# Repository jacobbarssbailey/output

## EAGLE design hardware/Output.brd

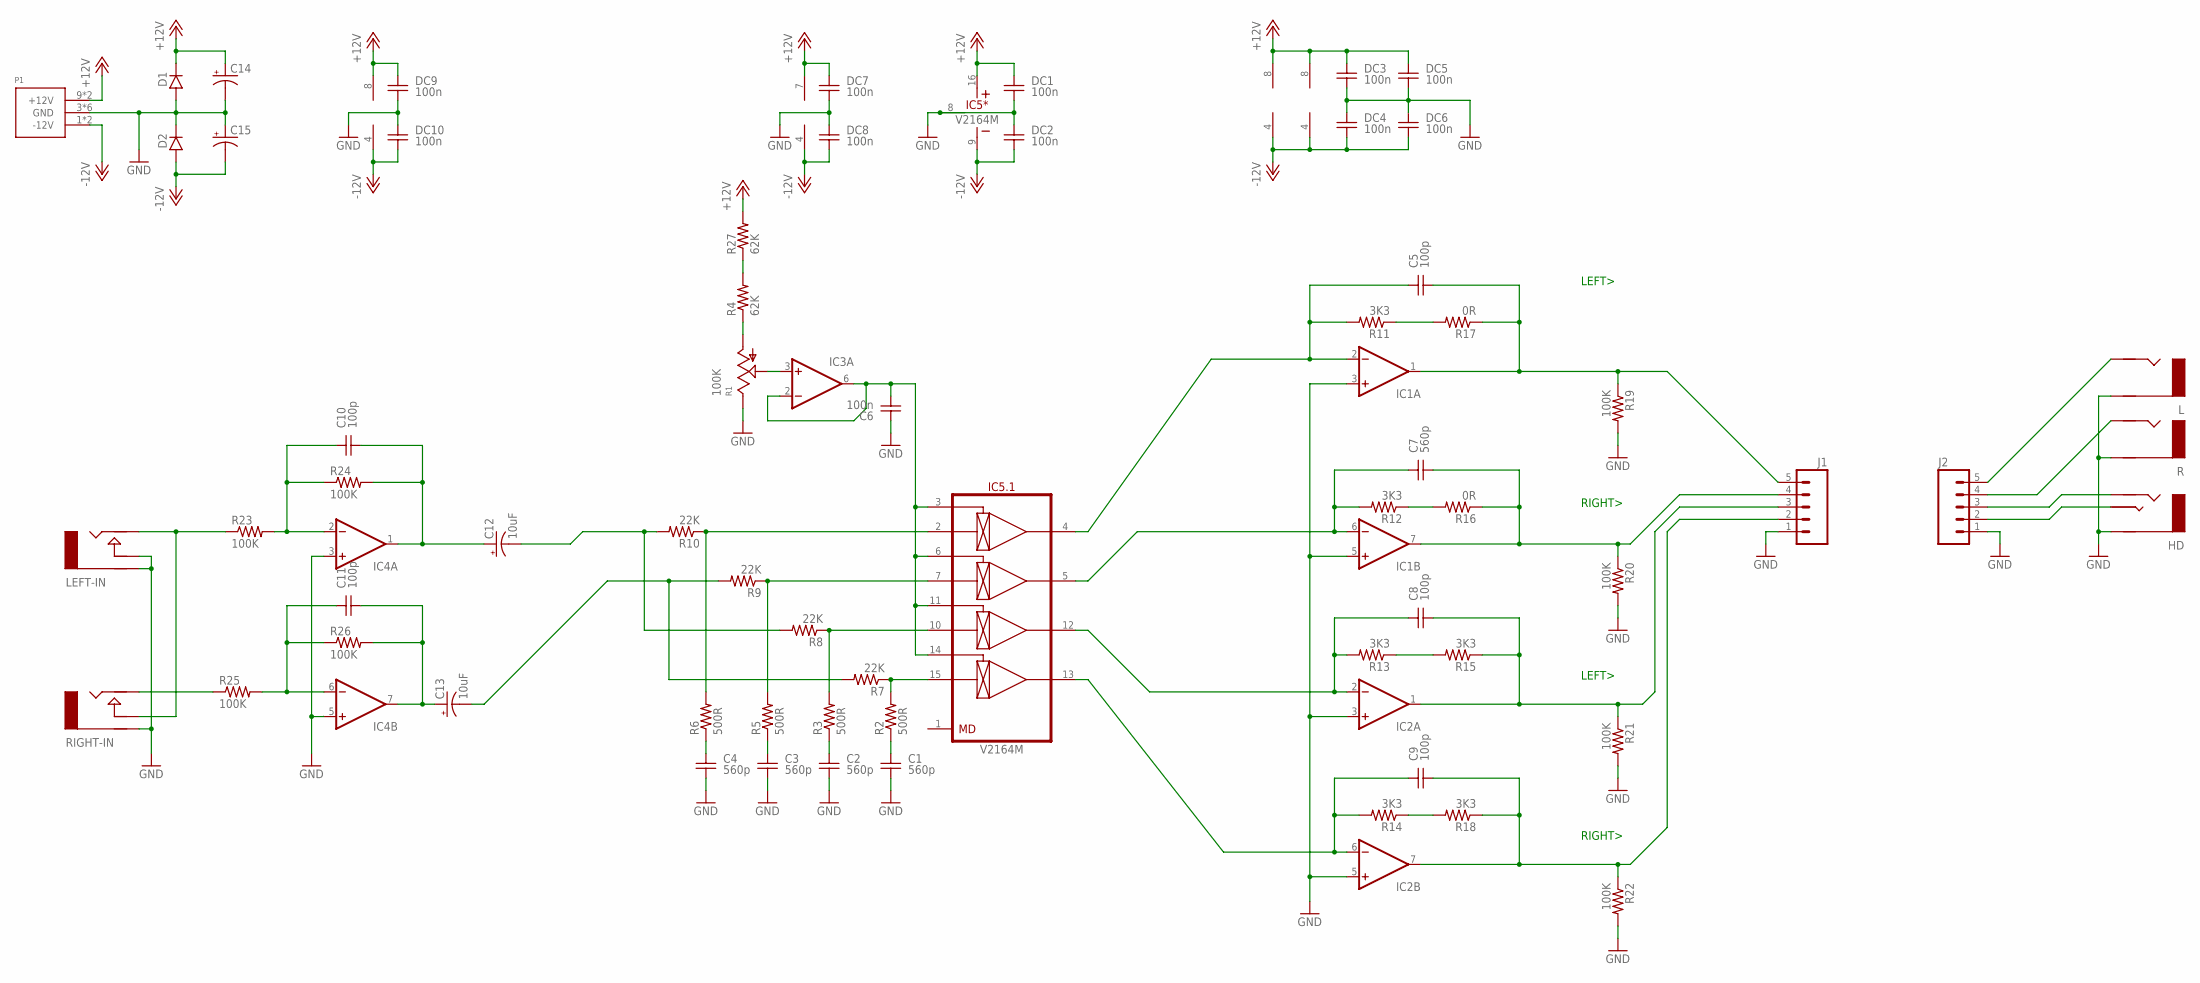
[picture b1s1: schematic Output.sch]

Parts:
C1, C2, C3, C4, C7: 560p; C-0805
C5, C8, C9, C10, C11: 100p; C-0805
C6: 100n; C-0805
C12, C13: 10uF; PANASONIC_C
C14, C15: CAP_POLPTH2; CPOL-RADIAL-10UF-25V
D1, D2: DIODESMA; SMA
DC1, DC2, DC3, DC4, DC5, DC6, DC7, DC8, DC9, DC10: 100n; C-0805
HD: AUDIO-JACK_STEREO; NJ3FD
IC1, IC2, IC4: OPAMP-DUAL; SO08
IC3: OPAMP-SINGLE; SO08
IC5: V2164M; SO-16
J1: CONN2; 1X05_LOCK
J2: CONN; 1X05_LOCK
L: AUDIO-JACK-MONO; NJ2FD
LEFT-IN: AUDIO-JACKINLINE; ERTHENVAR-JACK-INLINE
P1: POWER_SIMPLE10_SHROUDED; POWER_10_SHROUDED
R: AUDIO-JACK-MONO; NJ2FD
R1: 100K; POT-ALPHA-9MM
R2, R3, R5, R6: 500R; R-0805-MILL
R4, R27: 62K; R-0805-MILL
R7, R8, R9, R10: 22K; R-0805-MILL
R11, R12, R13, R14, R15, R18: 3K3; R-0805-MILL
R16, R17: 0R; R-0805-MILL
R19, R20, R21, R22, R23, R24, R25, R26: 100K; R-0805-MILL
RIGHT-IN: AUDIO-JACKINLINE; ERTHENVAR-JACK-INLINE

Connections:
+12V: C14.1 (+), D1.K (C), DC1.1, DC3.1, DC5.1, DC7.1, DC9.1, IC1.8 (V+), IC2.8 (V+), IC3.7 (V+), IC4.8 (V+), IC5.16 (V+), P1.9 (+12V), P1.10 (+12V), R27.P$2 (2)
-12V: C15.2 (-), D2.A, DC2.2, DC4.2, DC6.2, DC8.2, DC10.2, IC1.4 (V-), IC2.4 (V-), IC3.4 (V-), IC4.4 (V-), IC5.9 (V-), P1.1 (-12V), P1.2 (-12V)
GND: C1.2, C2.2, C3.2, C4.2, C6.1, C14.2 (-), C15.1 (+), D1.A, D2.K (C), DC1.2, DC2.1, DC3.2, DC4.1, DC5.2, DC6.1, DC7.2, DC8.1, DC9.2, DC10.1, HD.R (RING), IC1.3 (+IN), IC1.5 (+IN), IC2.3 (+IN), IC2.5 (+IN), IC4.3 (+IN), IC4.5 (+IN), IC5.8 (GND), J1.1, J2.1, L.S (RING), LEFT-IN.G (RING), LEFT-IN.N (NORM), P1.3 (GND), P1.4 (GND), P1.5 (GND), P1.6 (GND), P1.7 (GND), P1.8 (GND), R.S (RING), R1.B (E), R19.P$2 (2), R20.P$2 (2), R21.P$2 (2), R22.P$2 (2), RIGHT-IN.G (RING)
LEFT-IN: LEFT-IN.T (TIP), R23.P$1 (1), RIGHT-IN.N (NORM)
LEFT-IN-BUFF: C12.-, R8.P$2 (2), R10.P$2 (2)
unnamed: R1.A, R4.P$1 (1)
unnamed: IC5.2 (IN1), R6.P$2 (2), R10.P$1 (1)
unnamed: C6.2, IC3.2 (-IN), IC3.6 (OUT), IC5.3 (CV1), IC5.6 (CV2), IC5.11 (CV3), IC5.14 (CV4)
unnamed: IC5.7 (IN2), R5.P$2 (2), R9.P$1 (1)
unnamed: IC5.10 (IN3), R3.P$2 (2), R8.P$1 (1)
unnamed: IC5.15 (IN4), R2.P$2 (2), R7.P$1 (1)
unnamed: C1.1, R2.P$1 (1)
unnamed: J2.5, L.T (TIP)
unnamed: C2.1, R3.P$1 (1)
unnamed: C3.1, R5.P$1 (1)
unnamed: C4.1, R6.P$1 (1)
unnamed: R14.P$1 (1), R18.P$2 (2)
unnamed: C9.2, IC2.7 (OUT), J1.2, R18.P$1 (1), R22.P$1 (1)
unnamed: J2.4, R.T (TIP)
unnamed: C5.1, IC1.2 (-IN), IC5.4 (OUT1), R11.P$2 (2)
unnamed: C7.1, IC1.6 (-IN), IC5.5 (OUT2), R12.P$2 (2)
unnamed: C8.1, IC2.2 (-IN), IC5.12 (OUT3), R13.P$2 (2)
unnamed: C9.1, IC2.6 (-IN), IC5.13 (OUT4), R14.P$2 (2)
unnamed: C5.2, IC1.1 (OUT), J1.5, R17.P$1 (1), R19.P$1 (1)
unnamed: IC3.3 (+IN), R1.W (S)
unnamed: R13.P$1 (1), R15.P$2 (2)
unnamed: C7.2, IC1.7 (OUT), J1.4, R16.P$1 (1), R20.P$1 (1)
unnamed: R12.P$1 (1), R16.P$2 (2)
unnamed: C8.2, IC2.1 (OUT), J1.3, R15.P$1 (1), R21.P$1 (1)
unnamed: R11.P$1 (1), R17.P$2 (2)
unnamed: HD.T (TIP), J2.3
unnamed: HD.S (SLEEVE), J2.2
unnamed: C10.1, IC4.2 (-IN), R23.P$2 (2), R24.P$1 (1)
unnamed: C11.1, IC4.6 (-IN), R25.P$2 (2), R26.P$1 (1)
unnamed: C10.2, C12.+, IC4.1 (OUT), R24.P$2 (2)
unnamed: C11.2, C13.+, IC4.7 (OUT), R26.P$2 (2)
unnamed: R4.P$2 (2), R27.P$1 (1)
RIGHT-IN: R25.P$1 (1), RIGHT-IN.T (TIP)
RIGHT-IN-BUFF: C13.-, R7.P$2 (2), R9.P$2 (2)

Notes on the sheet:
LEFT>
RIGHT>

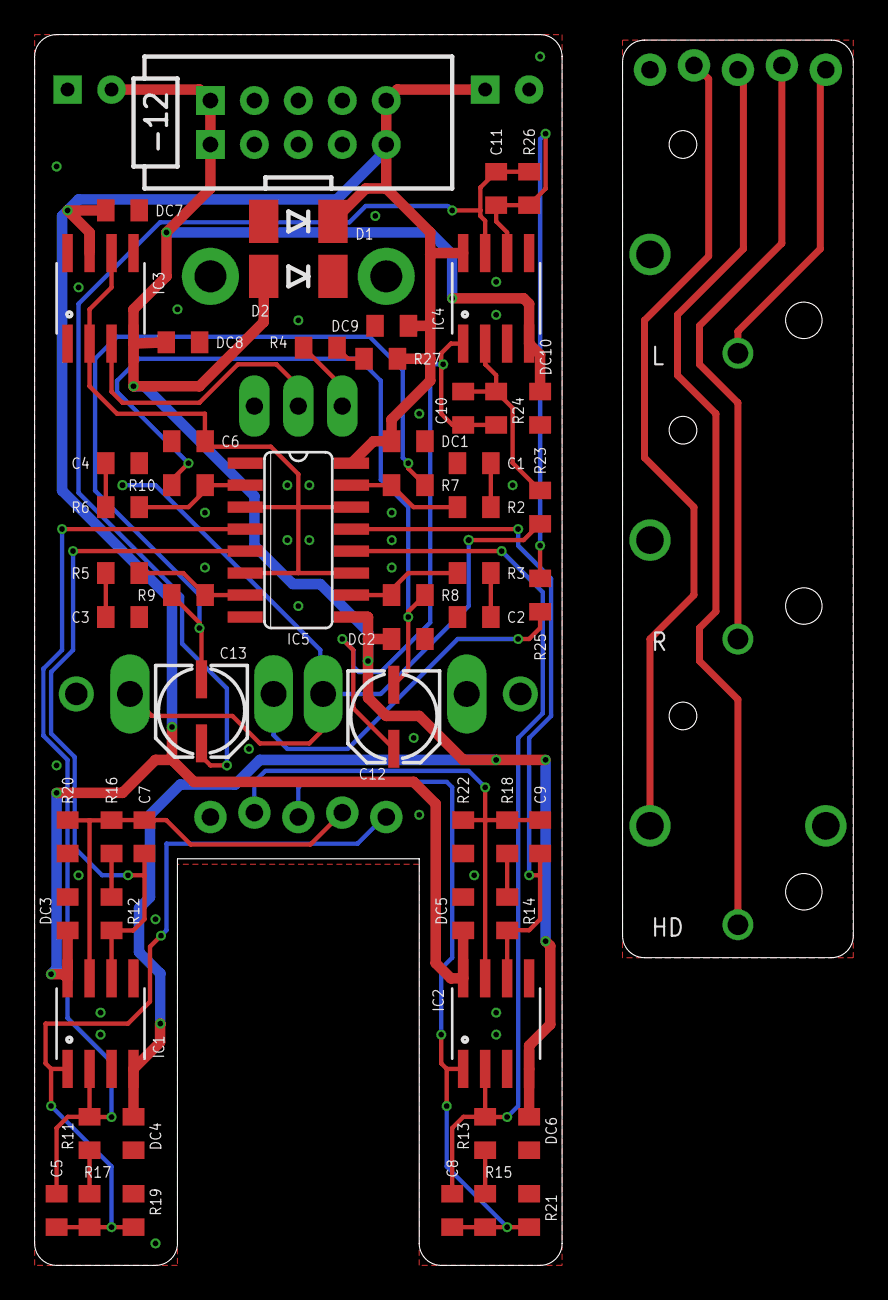
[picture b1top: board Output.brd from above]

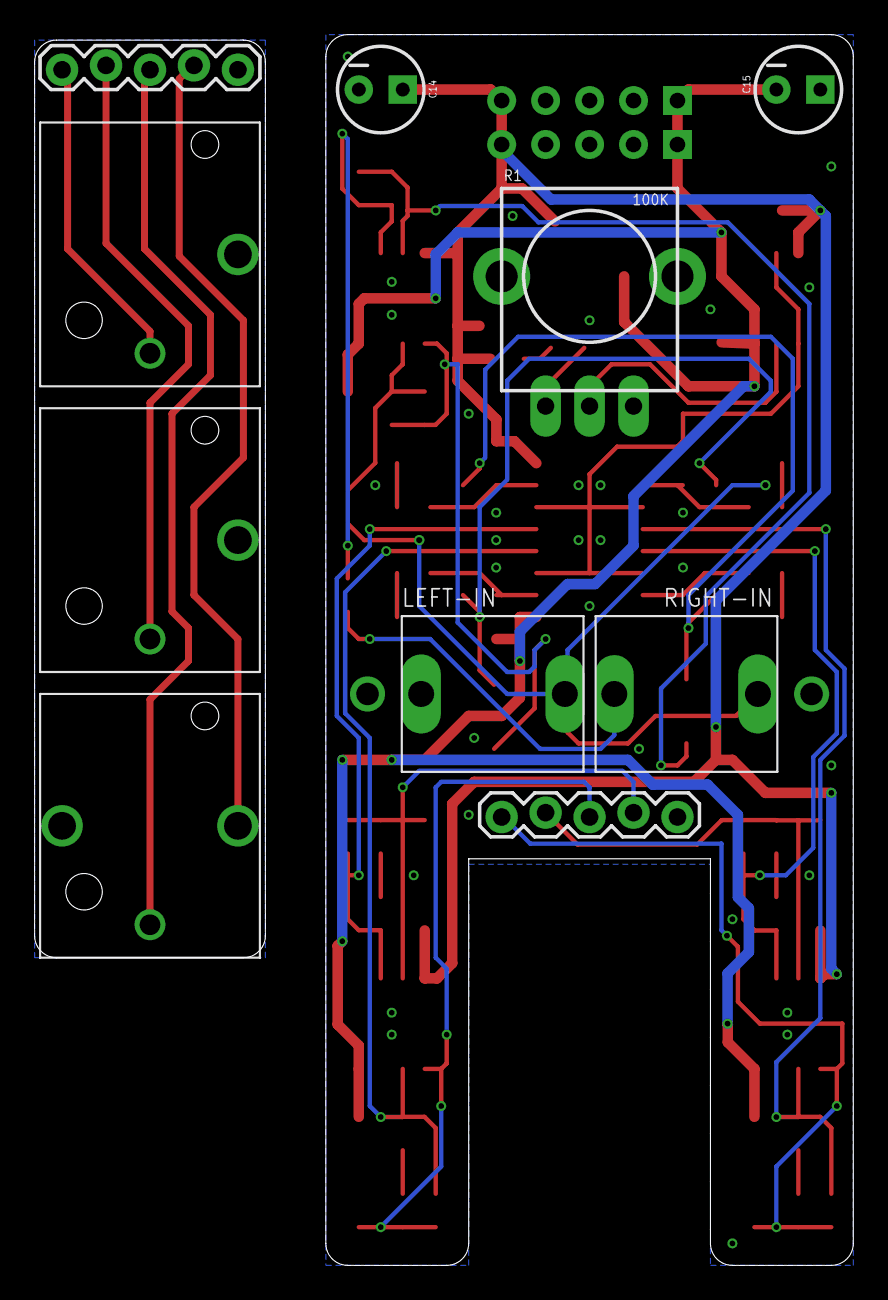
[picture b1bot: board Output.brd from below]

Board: 2 copper layers, 30.5 x 71.1 mm, 67 parts (10 on the bottom side), 39 nets.

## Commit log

2019-08-17 init
2019-08-17 readme
2019-08-17 front panel design

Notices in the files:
parts and their libraries:
SparkFun-Connectors: Licensing: Creative Commons ShareAlike 4.0 International - https://creativecommons.org/licenses/by-sa/4.0
